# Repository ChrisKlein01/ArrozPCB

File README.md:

# IoT System for Water Management in Rice Paddies

Embedded IoT system for LoRa + GPS telemetry, integrating custom hardware, embedded firmware, iterative PCB design, and a Node-RED backend.

## Final Prototype (V3)

The following images show selected views of the final hardware prototype (V3).

### Enclosure

### Custom PCB

### Auxiliary Modules
For example, Power management and USB to UART modules.

<h2>Firmware Flow Diagram</h2>

## System Overview

End-to-end IoT prototype for wireless telemetry using LoRa communication and GPS data acquisition, covering proof-of-concept validation, custom hardware development, embedded firmware, iterative PCB design, and a complete Node-RED data processing pipeline.

---

## Repository Structure

- `Codigo_lilygo/`  
  Proof-of-concept implementation using a LilyGO T3 v1.6.1 development board. Used for early validation of LoRa communication and end-to-end data flow through an initial Node-RED pipeline before custom PCB and GPS integration.

- `Firmware/`  
  Main embedded firmware for the custom PCB. Handles GPS acquisition, LoRa communication, and system logic.

- `Node Red/`  
  Node-RED flows for telemetry ingestion, processing, and visualization.

- `Envolvente/`  
  Mechanical enclosure design for system housing and protection.

- `V1.0/`  
  First PCB iteration used to validate the custom LoRa hardware.

- `V2.0/`  
  PCB redesign incorporating GPS integration and correcting initial hardware issues.

- `V3.0/`  
  Final PCB revision with optimized layout and complete system integration.

- `.gitignore`  
  Git ignore rules for build artifacts and temporary files.

- `README.md`  
  Project documentation.

---

## Development Flow

1. Proof-of-concept on a LilyGO T3 development board.
2. Validation of LoRa communication and the initial telemetry pipeline using Node-RED.
3. Design and validation of the first custom PCB (V1.0).
4. PCB redesign with GPS integration and hardware improvements (V2.0).
5. Final optimized hardware revision with complete system integration (V3.0).
6. Integration with the Node-RED backend and end-to-end system validation.

---

## Project Scope

The project covers the complete development cycle of an embedded IoT system, including:

- Embedded firmware development (C/C++)
- Custom electronic circuit design
- Schematic capture and PCB design (KiCad)
- PCB assembly and soldering
- LoRa wireless communication
- GPS integration
- MQTT-based telemetry
- Node-RED backend development
- Mechanical enclosure design

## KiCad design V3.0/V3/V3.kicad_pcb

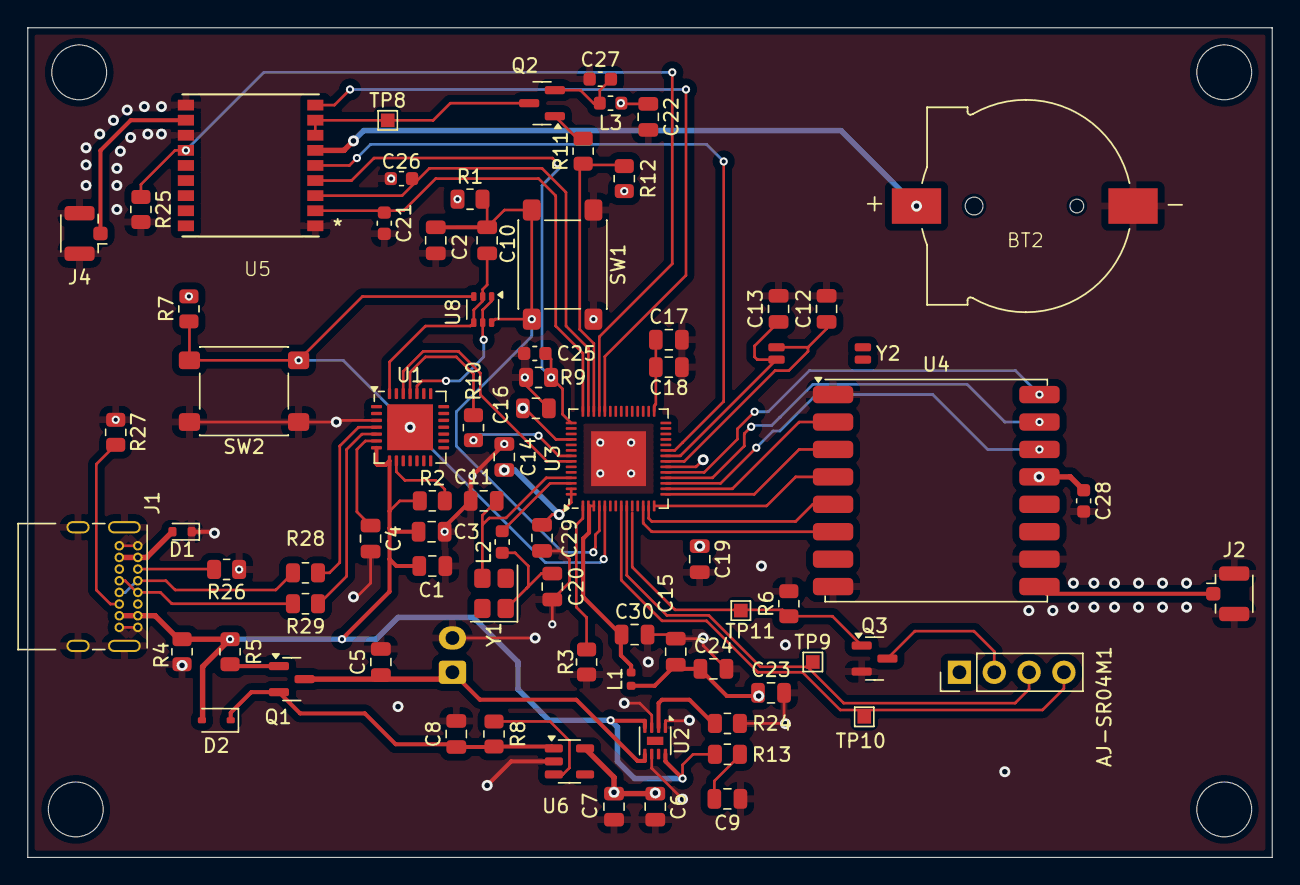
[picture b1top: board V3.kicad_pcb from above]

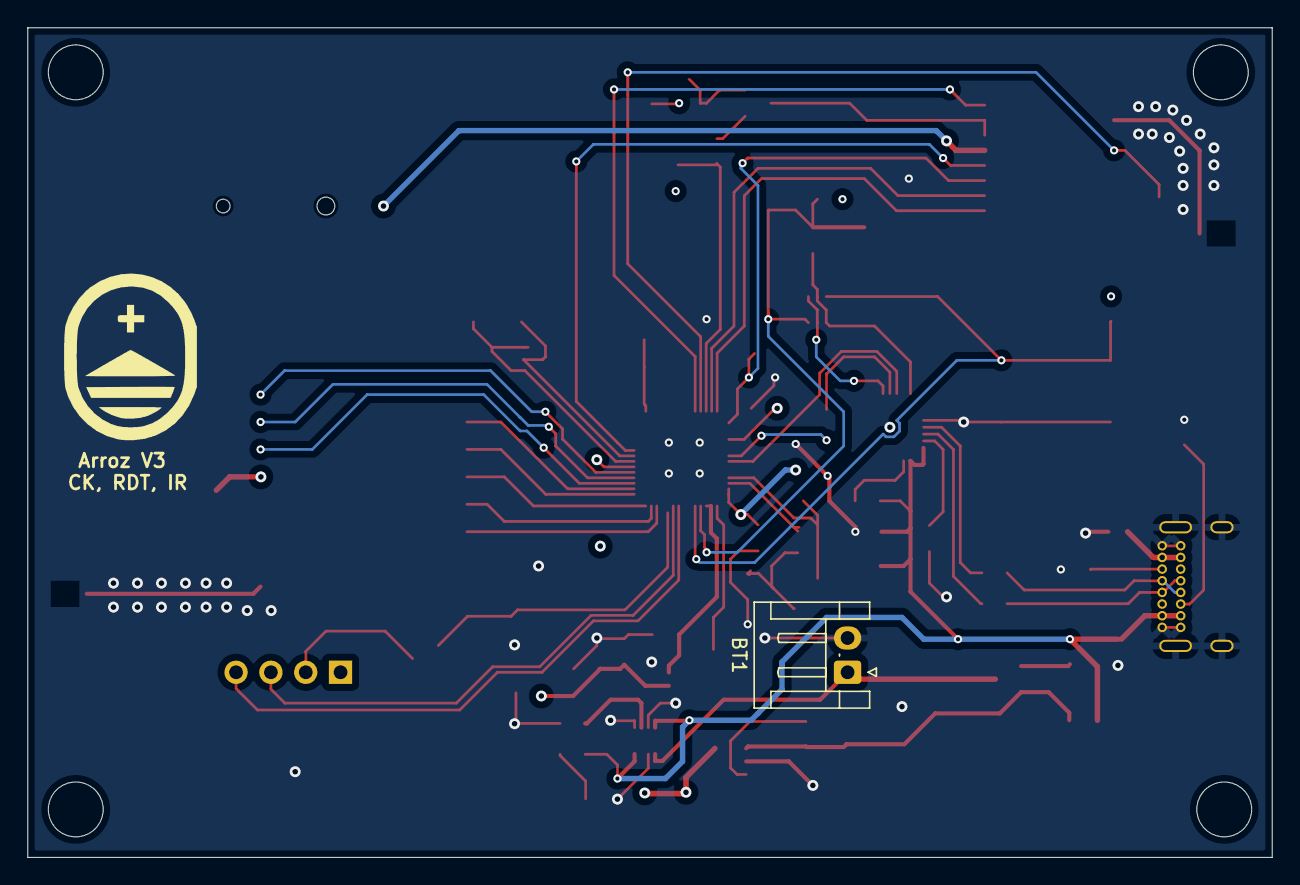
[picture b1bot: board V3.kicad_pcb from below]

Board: 4 copper layers, 90.8 x 60.5 mm, 79 parts (2 on the bottom side), 57 nets.

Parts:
AJ-SR04M1: U3; PinHeader_1x04_P2.54mm_Vertical
BT1: Battery; JST_EH_S2B-EH_1x02_P2.50mm_Horizontal
BT2: 1056TR; pila
C1, C4, C7, C8, C14, C17: 1u; C_0805_2012Metric
C2: 2.2u; C_0805_2012Metric
C3, C10, C16, C18, C19, C30: 0.1u; C_0805_2012Metric
C5, C6, C9, C23: 10u; C_0805_2012Metric
C11: 15p; C_0805_2012Metric
C12, C13: 4.7p; C_0805_2012Metric
C15: 2.2p; C_0805_2012Metric
C20: 18p; C_0805_2012Metric
C21, C25, C26, C27: 56pF; C_0603_1608Metric
C22: 10nF; C_0805_2012Metric
C24: 1.8p; C_0805_2012Metric
C28: 10u; C_0603_1608Metric
C29: 10n; C_0805_2012Metric
D1: RSB6.8S; D_SOD-523
D2: 1N5817WS; D_SOD-323
J1: USB_C_Receptacle_USB2.0_16P; USB_C_Receptacle_GCT_USB4085
J2, J4: Conn_Coaxial_Small; U.FL_Hirose_U.FL-R-SMT-1_Vertical
L1: 2.0n; L_0402_1005Metric
L2: 22n; L_0603_1608Metric
L3: 27nH; L_0603_1608Metric
Q1: AO3401; SOT-23
Q2: AO3401A; SOT-23
Q3: AO3400A; SOT-23
R1, R4, R7, R12, R25: 10k; R_0805_2012Metric
R2: 4.7k; R_0805_2012Metric
R3: 50 NC; R_0805_2012Metric
R5, R11: 1k; R_0805_2012Metric
R6, R8, R9: 100k; R_0805_2012Metric
R10: 499; R_0805_2012Metric
R13: 1R; R_0805_2012Metric
R24: 2k; R_0805_2012Metric
R26, R27: 5.1k; R_0805_2012Metric
R28, R29: 22; R_0805_2012Metric
SW1, SW2: SW_Push; SW_SPST_PTS645Sx43SMTR92
TP8, TP9, TP10, TP11: TestPoint; TestPoint_Pad_1.0x1.0mm
U1: CP2102; QFN-28-1EP_5x5mm_P0.5mm_EP3.35x3.35mm
U2: LGS4056HDA1; DFN-8-1EP_2x2mm_P0.5mm_EP0.6x1.2mm
U3: ESP32-S3FN8; QFN-56-1EP_7x7mm_P0.4mm_EP4x4mm
U4: RFM95W-915S2; HOPERF_RFM9XW_SMD
U5: TESEO-LIV3R; Teseo
U6: AP2112K-3.3TRG1; SOT-23-5
U8: 2n7002bks; SOT-363_SC-70-6
UCU: LOGO; LogoUCU
Y1: Crystal 40MHz/10ppm; Crystal_SMD_3225-4Pin_3.2x2.5mm
Y2: 32.768KHz/ESR≤70KΩ; Crystal_SMD_SeikoEpson_MC146-4Pin_6.7x1.5mm

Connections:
32K_XN: C13.1, U3.22 (XTAL_32K_N), Y2.1
32K_XP: C12.1, U3.21 (XTAL_32K_P), Y2.4
AntOff_GPS: R25.1, U3.39 (GPIO34), U5.13 (ANT_OFF)
CADdetect_LoRa: U3.19 (GPIO14), U4.16 (DIO2)
CHIP_PU: C2.1, C10.1, R1.2, SW1.2, U3.4 (CHIP_PU), U8.6 (D1)
DTR: C10.2, U1.28 (~DTR), U8.2 (G1), U8.4 (S2)
D_N: R29.1, U1.5 (D-)
D_P: R28.1, U1.4 (D+)
ECHO_Sensor: AJ-SR04M1.4 (ECHO), TP10.1, U3.8 (GPIO3)
GND: BT1.2 (-), BT2.N, C1.2, C2.2, C3.2, C4.2, C5.2, C6.2, C7.2, C8.2, C9.2, C11.2, C12.2, C13.2, C14.2, C15.2, C16.2, C17.2, C18.2, C19.2, C20.2, C21.2, C22.2, C23.2, C24.2, C25.2, C26.2, C27.1, C28.2, C29.2, C30.2, D1.1 (K), J1.A1 (GND), J1.A12 (GND), J1.B1 (GND), J1.B12 (GND), J1.S1 (SHIELD), J2.2 (Ext), J4.2 (Ext), Q3.2 (S), R3.2, R4.2, R6.2, R9.2, R24.1, R25.2, R26.1, R27.1, SW1.1, SW2.1, U1.3 (GND), U1.29 (GND), U2.1 (Temp), U2.3 (Gnd), U2.6 (DONE), U3.57 (GND), U4.1 (GND), U4.8 (GND), U4.10 (GND), U5.1 (GND), U5.10 (GND_RF), U5.12 (GND_RF), U6.2 (GND)
MISO_LoRa: U3.15 (GPIO10), U4.3 (MOSI)
MOSI_LoRa: U3.16 (GPIO11), U4.2 (MISO)
NSS_LoRa: U3.13 (GPIO8), U4.5 (NSS)
unnamed: AJ-SR04M1.2 (GND), Q3.3 (D)
unnamed: C9.1, R13.1
unnamed: C30.1, L1.2, U3.2 (VDD3P3), U3.3 (VDD3P3)
unnamed: C8.1, D2.1 (K), Q1.2 (S), R8.1, U6.1 (IN)
unnamed: J1.A5 (CC1), R26.2
unnamed: J1.B5 (CC2), R27.2
unnamed: J1.A6 (D+), J1.B6 (D+), R28.2
unnamed: J1.A7 (D-), J1.B7 (D-), R29.2
unnamed: J2.1 (In), U4.9 (ANT)
unnamed: J4.1 (In), U5.11 (RF_IN)
unnamed: Q1.1 (G), R5.2
unnamed: Q2.3 (D), TP8.1, U5.7 (VCC_IO), U5.8 (VCC)
unnamed: C27.2, L3.2, Q2.2 (S)
unnamed: C4.1, U1.6 (VDD)
unnamed: R2.2, U1.9 (~RST)
unnamed: R24.2, U2.2 (Prog)
unnamed: R11.1, R12.1, U3.40 (GPIO35)
unnamed: R3.1, U3.1 (LNA_IN)
unnamed: R10.2, U3.49 (U0TXD)
unnamed: C17.1, C18.1, U3.29 (VDD_SPI)
unnamed: L2.2, U3.54 (XTAL_P)
unnamed: R8.2, U6.3 (EN)
PPS_GPS: C25.1, R9.1, U3.43 (GPIO38), U5.4 (1PPS)
PWR_Sensor: Q3.1 (G), R6.1, TP11.1, U3.10 (GPIO5)
Pnp_Gps: Q2.1 (G), R11.2
RTS: U1.24 (~RTS), U8.1 (S1), U8.5 (G2)
RXtimeout_LoRa: U3.18 (GPIO13), U4.15 (DIO1)
RX/TXdone_LoRa: U3.17 (GPIO12), U4.14 (DIO0)
Reset_GPS: U3.38 (GPIO33), U5.9 (SYS_RSTn)
Reset_LoRa: U3.12 (GPIO7), U4.6 (RESET)
Rx_GPS: C26.1, U3.41 (GPIO36), U5.3 (RX)
SCK_LoRa: U3.14 (GPIO9), U4.4 (SCK)
TRIG_Sensor: AJ-SR04M1.3 (TRIG), TP9.1, U3.9 (GPIO4)
Tx_GPS: C21.1, U3.42 (GPIO37), U5.2 (TX)
U0RXD: U1.26 (TXD), U3.50 (U0RXD)
U0TXD: R10.1, U1.25 (RXD)
USER_KEY: R7.1, SW2.2, U3.5 (GPIO0), U8.3 (D2)
VBAT: BT1.1 (+), C5.1, Q1.3 (D), U2.5 (BAT)
VBatt: BT2.P, U5.6 (VBATT)
VDD_3V3: AJ-SR04M1.1 (5V), C6.1, C7.1, C14.1, C15.1, C16.1, C19.1, C22.1, C23.1, C24.1, C28.1, C29.1, L1.1, L3.1, R1.1, R7.2, R12.2, U3.20 (VDD3P3_RTC), U3.46 (VDD3P3_CPU), U3.55 (VDDA), U3.56 (VDDA), U4.13 (3.3V), U6.5 (OUT)
VDD_5V: C1.1, C3.1, D1.2 (A), D2.2 (A), J1.A4 (VBUS), J1.A9 (VBUS), J1.B4 (VBUS), J1.B9 (VBUS), R2.1, R4.1, R5.1, R13.2, U1.7 (VREGIN), U1.8 (VBUS), U2.4 (Vcc), U2.8 (CE)
Wake_GPS: U3.23 (GPIO17), U5.5 (Wake-Up)
XTAL_N: C11.1, U3.53 (XTAL_N), Y1.3
XTAL_P: C20.1, L2.1, Y1.1

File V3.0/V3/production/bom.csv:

Designator,Footprint,Quantity,Value,LCSC Part #
AJ-SR04M1,PinHeader_1x04_P2.54mm_Vertical,1,U3,C7243
BT1,JST_EH_S2B-EH_1x02_P2.50mm_Horizontal,1,Battery,
BT2,pila,1,1056TR,C238068
"C1, C14, C17, C4, C7, C8",0805,6,1u,
"C10, C16, C18, C19, C3, C30",0805,6,0.1u,
C11,0805,1,15p,
"C12, C13",0805,2,4.7p,
C15,0805,1,2.2p,
C2,0805,1,2.2u,
C20,0805,1,18p,
"C21, C25, C26, C27",0603,4,56pF,
C22,0805,1,10nF,
"C23, C5, C6, C9",0805,4,10u,
C24,0805,1,1.8p,
C28,0603,1,10u,
C29,0805,1,10n,
D1,D_SOD-523,1,RSB6.8S,C28646388
D2,D_SOD-323,1,1N5817WS,C727114
J1,USB_C_Receptacle_GCT_USB4085,1,USB_C_Receptacle_USB2.0_16P,C7095263
"J2, J4",U.FL_Hirose_U.FL-R-SMT-1_Vertical,2,Conn_Coaxial_Small,C88373
L1,0402,1,2.0n,C18216
L2,0603,1,22n,C12099
L3,0603,1,27nH,C12100
Q1,SOT-23,1,AO3401,C181091
Q2,SOT-23,1,AO3401A,C15127
Q3,SOT-23,1,AO3400A,C20917
"R1, R12, R25, R4, R7",0805,5,10k,
R10,0805,1,499,
"R11, R5",0805,2,1k,
R13,0805,1,1R,
R2,0805,1,4.7k,
R24,0805,1,2k,
"R26, R27",0805,2,5.1k,
"R28, R29",0805,2,22,
R3,0805,1,50 NC,
"R6, R8, R9",0805,3,100k,
"SW1, SW2",SW_SPST_PTS645Sx43SMTR92,2,SW_Push,C49234152
"TP10, TP11, TP8, TP9",TestPoint_Pad_1.0x1.0mm,4,TestPoint,
U1,QFN-28-1EP_5x5mm_P0.5mm_EP3.35x3.35mm,1,CP2102,C6568
U2,DFN-8-1EP_2x2mm_P0.5mm_EP0.6x1.2mm,1,LGS4056HDA1,C5124109
U3,QFN-56-1EP_7x7mm_P0.4mm_EP4x4mm,1,ESP32-S3FN8,C2913196
U4,HOPERF_RFM9XW_SMD,1,RFM95W-915S2,
U5,Teseo,1,TESEO-LIV3R,
U6,SOT-23-5,1,AP2112K-3.3TRG1,C23380830
U8,SOT-363_SC-70-6,1,2n7002bks,C68181
Y1,Crystal_SMD_3225-4Pin_3.2x2.5mm,1,Crystal 40MHz/10ppm,C5380316
Y2,Crystal_SMD_SeikoEpson_MC146-4Pin_6.7x1.5mm,1,32.768KHz/ESR≤70KΩ,C15482

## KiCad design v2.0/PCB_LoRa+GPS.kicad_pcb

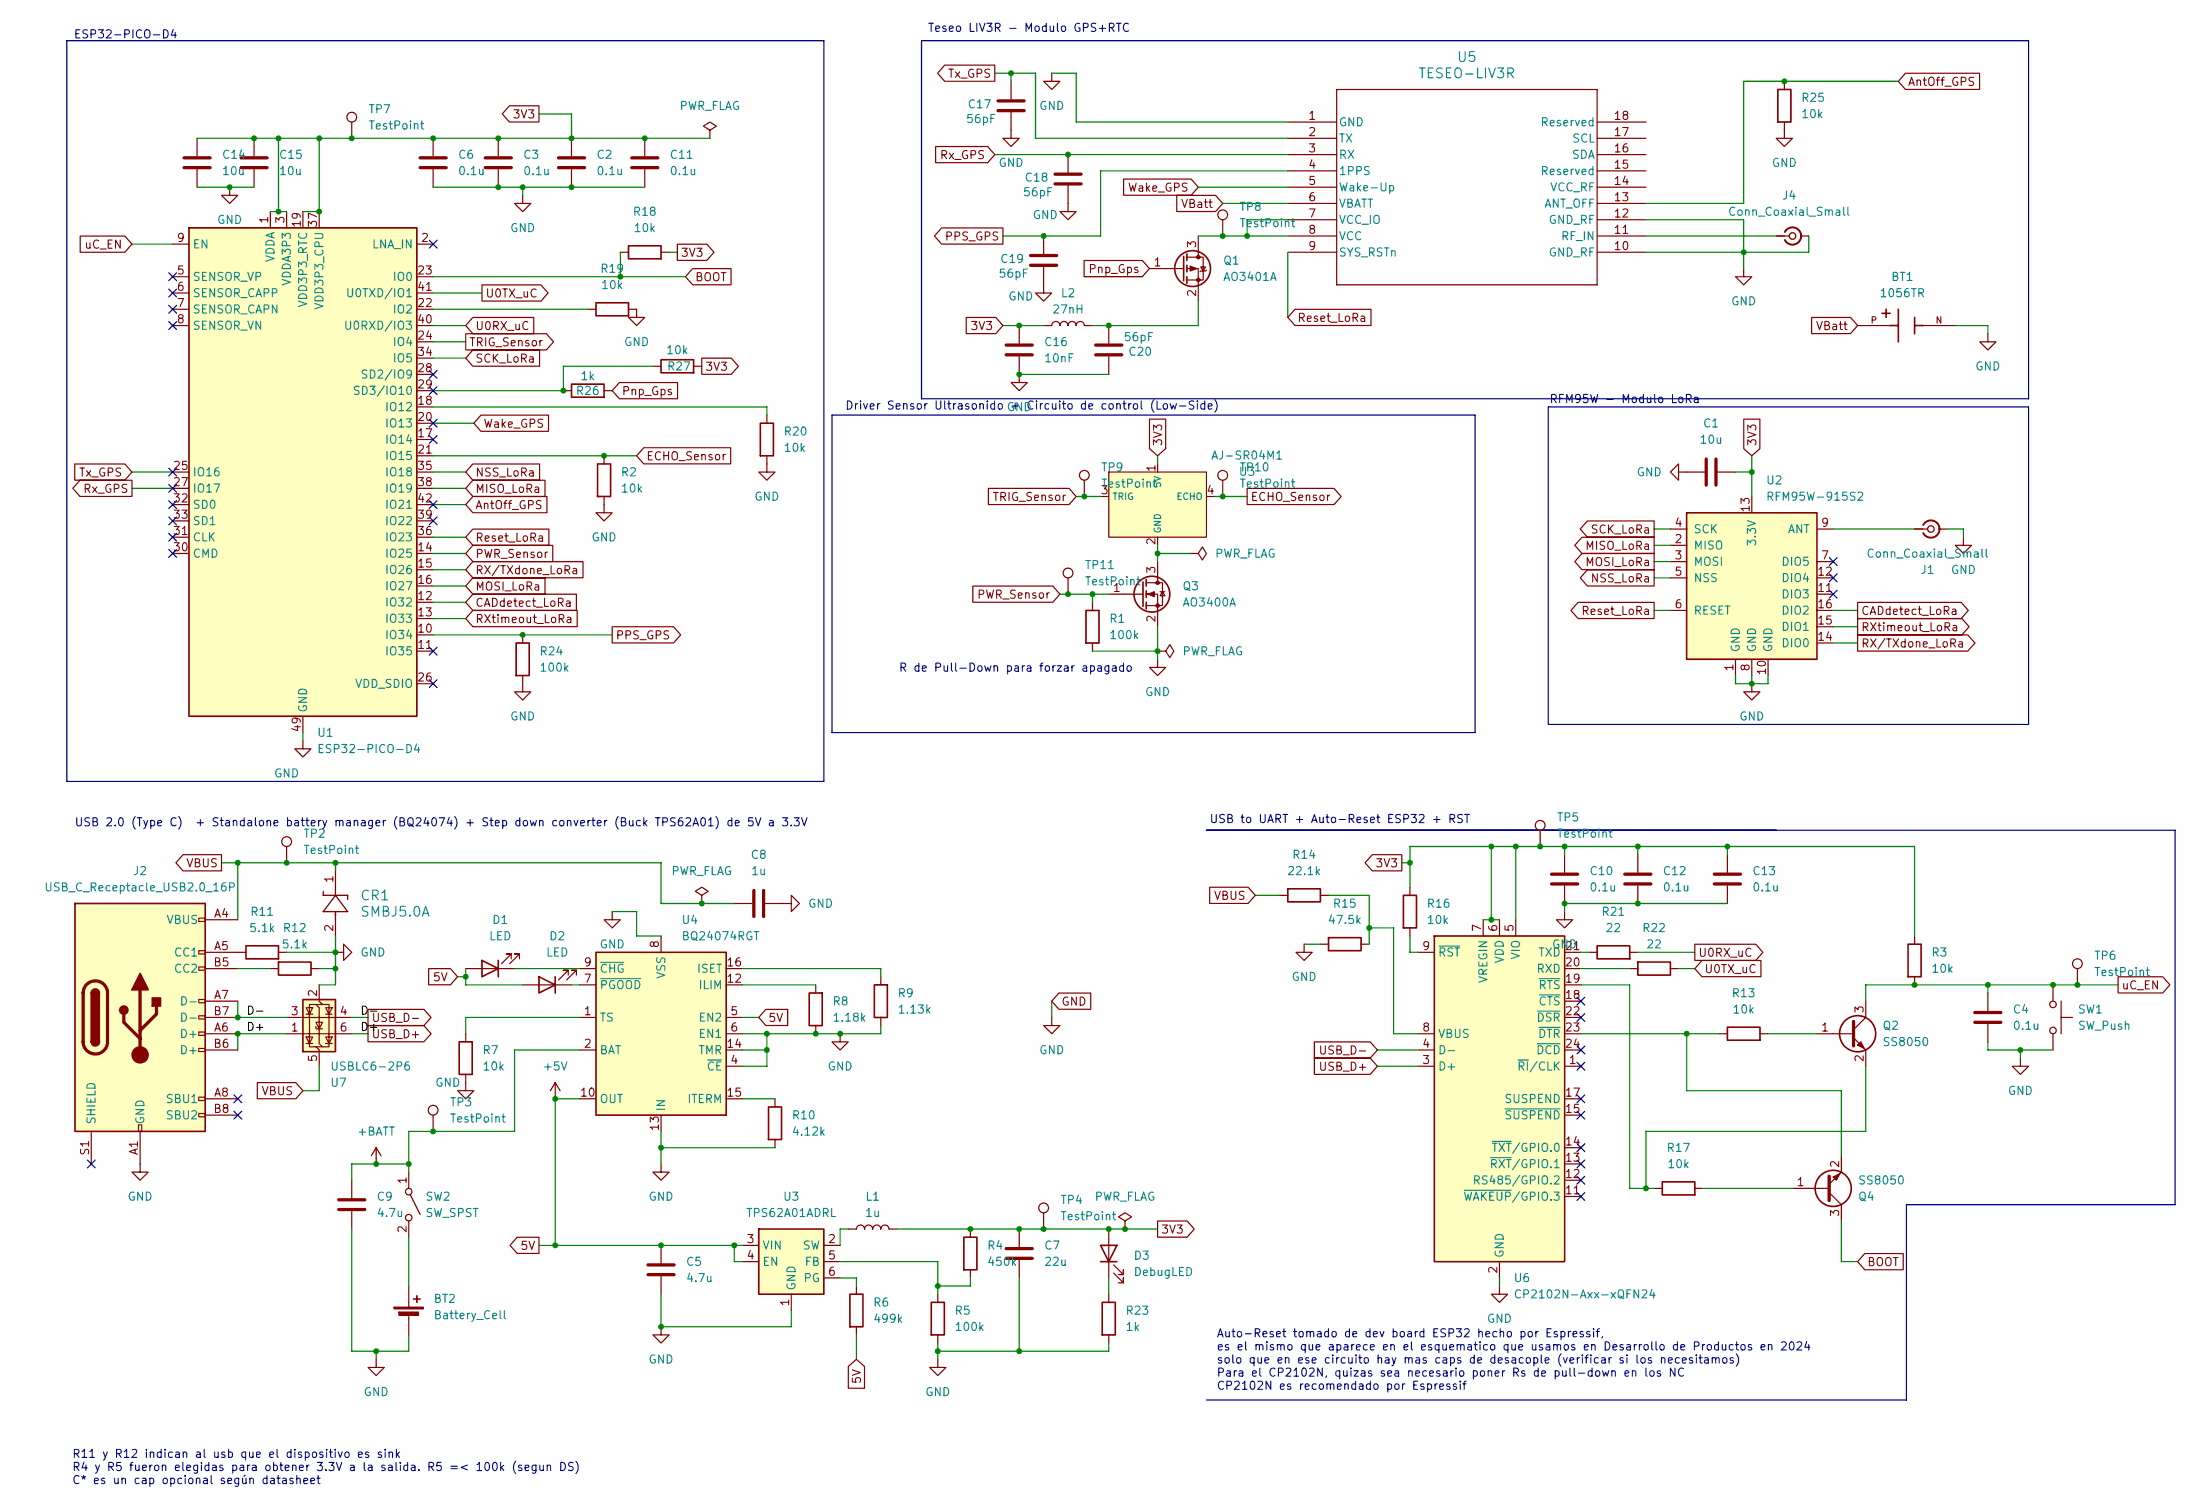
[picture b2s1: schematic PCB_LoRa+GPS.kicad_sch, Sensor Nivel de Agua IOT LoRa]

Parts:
AJ-SR04M1: U3; PinSocket_1x04_P1.00mm_Vertical
BT1: 1056TR; BAT_1056TR; PARTREV D
BT2: Battery_Cell; JST_EH_S2B-EH_1x02_P2.50mm_Horizontal
C1, C14, C15: 10u; C_0603_1608Metric
C2, C3, C4, C6, C10, C11, C12, C13: 0.1u; C_0402_1005Metric
C5: 4.7u; C_0603_1608Metric
C7: 22u; C_0805_2012Metric
C8: 1u; C_0402_1005Metric
C9: 4.7u; C_0402_1005Metric
C16: 10nF; C_0805_2012Metric
C17, C18, C19, C20: 56pF; C_0603_1608Metric
CR1: SMBJ5.0A; D_SMB
D1, D2: LED; LED_0603_1608Metric
D3: DebugLED; LED_0603_1608Metric
J1, J4: Conn_Coaxial_Small; U.FL_Hirose_U.FL-R-SMT-1_Vertical
J2: USB_C_Receptacle_USB2.0_16P; USB_C_Receptacle_GCT_USB4085
L1: 1u; L_0805_2012Metric
L2: 27nH; L_0805_2012Metric
Q1: AO3401A; SOT-23
Q2, Q4: SS8050; SOT-23
Q3: AO3400A; SOT-23
R1, R5, R24: 100k; R_0402_1005Metric
R2, R3, R7, R13, R16, R17, R18, R19, R20, R25, R27: 10k; R_0402_1005Metric
R4: 450k; R_0402_1005Metric
R6: 499k; R_0402_1005Metric
R8: 1.18k; R_0402_1005Metric
R9: 1.13k; R_0402_1005Metric
R10: 4.12k; R_0402_1005Metric
R11, R12: 5.1k; R_0402_1005Metric
R14: 22.1k; R_0402_1005Metric
R15: 47.5k; R_0402_1005Metric
R21, R22: 22; R_0402_1005Metric
R23, R26: 1k; R_0402_1005Metric
SW1: SW_Push; SW_Push_1P1T_NO_CK_KMR2
SW2: SW_SPST; SW_E-Switch_EG1271_SPDT
TP2, TP3, TP4, TP5, TP6, TP7, TP8, TP9, TP10, TP11: TestPoint; TestPoint_Pad_1.0x1.0mm
U1: ESP32-PICO-D4; QFN-48-1EP_7x7mm_P0.5mm_EP5.3x5.3mm
U2: RFM95W-915S2; HOPERF_RFM9XW_SMD
U3: TPS62A01ADRL; SOT-563
U4: BQ24074RGT; VQFN-16-1EP_3x3mm_P0.5mm_EP1.6x1.6mm
U5: TESEO-LIV3R; ARRAY_LIV3R_STM
U6: CP2102N-Axx-xQFN24; QFN-24-1EP_4x4mm_P0.5mm_EP2.6x2.6mm
U7: USBLC6-2P6; SOT-666

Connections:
3V3: AJ-SR04M1.1 (5V), C1.1, C2.1, C3.1, C6.1, C7.1, C10.1, C11.1, C12.1, C13.1, C14.1, C15.1, C16.1, D3.2 (A), L1.2, L2.1, R3.1, R4.1, R16.1, R18.2, R27.2, TP4.1, TP5.1, TP7.1, U1.1 (VDDA), U1.3 (VDDA3P3), U1.4 (VDDA3P3), U1.19 (VDD3P3_RTC), U1.37 (VDD3P3_CPU), U1.43 (VDDA), U1.46 (VDDA), U2.13 (3.3V), U6.5 (VIO), U6.6 (VDD), U6.7 (VREGIN)
5V: C5.1, D1.2 (A), D2.2 (A), R6.2, U3.3 (VIN), U3.4 (EN), U4.5 (EN2), U4.10 (OUT), U4.11 (OUT)
+BATT: C9.1, SW2.1 (A), TP3.1, U4.2 (BAT), U4.3 (BAT)
AntOff_GPS: R25.1, U1.42 (IO21), U5.13 (ANT_OFF)
BOOT: Q4.3 (C), R18.1, U1.23 (IO0)
CADdetect_LoRa: U1.12 (IO32), U2.16 (DIO2)
ECHO_Sensor: AJ-SR04M1.4 (ECHO), R2.1, TP10.1, U1.21 (IO15)
GND: BT1.N, BT2.2 (-), C1.2, C2.2, C3.2, C4.2, C5.2, C6.2, C7.2, C8.1, C9.2, C10.2, C11.2, C12.2, C13.2, C14.2, C15.2, C16.2, C17.2, C18.2, C19.2, C20.1, CR1.2, J1.2 (Ext), J2.A1 (GND), J2.A12 (GND), J2.B1 (GND), J2.B12 (GND), J4.2 (Ext), Q3.2 (S), R1.2, R2.2, R5.2, R7.1, R8.1, R9.1, R10.2, R11.2, R12.1, R15.2, R19.2, R20.2, R23.2, R24.2, R25.2, SW1.2, U1.49 (GND), U2.1 (GND), U2.8 (GND), U2.10 (GND), U3.1 (GND), U4.4 (~CE), U4.6 (EN1), U4.8 (VSS), U4.13 (IN), U4.14 (TMR), U4.17 (VSS), U5.1 (GND), U5.10 (GND_RF), U5.12 (GND_RF), U6.2 (GND), U6.25 (GND), U7.2 (GND); also elsewhere on the board
MISO_LoRa: U1.38 (IO19), U2.2 (MISO)
MOSI_LoRa: U1.16 (IO27), U2.3 (MOSI)
NSS_LoRa: U1.35 (IO18), U2.5 (NSS)
unnamed: AJ-SR04M1.2 (GND), Q3.3 (D)
unnamed: BT2.1 (+), SW2.2 (B)
unnamed: D1.1 (K), U4.9 (~CHG)
unnamed: D2.1 (K), U4.7 (~PGOOD)
unnamed: D3.1 (K), R23.1
unnamed: J1.1 (In), U2.9 (ANT)
unnamed: J2.A5 (CC1), R11.1
unnamed: J2.B5 (CC2), R12.2
unnamed: J4.1 (In), U5.11 (RF_IN)
unnamed: Q1.3 (D), TP8.1, U5.7 (VCC_IO), U5.8 (VCC)
unnamed: C20.2, L2.2, Q1.2 (S)
unnamed: Q2.1 (B), R13.2
unnamed: Q2.2 (E), R17.1, U6.19 (~RTS)
unnamed: Q4.1 (B), R17.2
unnamed: Q4.2 (E), R13.1, U6.23 (~DTR)
unnamed: R19.1, U1.22 (IO2)
unnamed: R20.1, U1.18 (IO12)
unnamed: R4.2, R5.1, U3.5 (FB)
unnamed: R6.1, U3.6 (PG)
unnamed: L1.1, U3.2 (SW)
unnamed: R8.2, U4.12 (ILIM)
unnamed: R9.2, U4.16 (ISET)
unnamed: R10.1, U4.15 (ITERM)
unnamed: R7.2, U4.1 (TS)
unnamed: R22.2, U6.20 (RXD)
unnamed: R21.1, U6.21 (TXD)
unnamed: R14.1, R15.1, U6.8 (VBUS)
unnamed: R16.2, U6.9 (~RST)
PPS_GPS: C19.1, R24.1, U1.10 (IO34), U5.4 (1PPS)
PWR_Sensor: Q3.1 (G), R1.1, TP11.1, U1.14 (IO25)
Pnp_Gps: Q1.1 (G), R26.2
RXtimeout_LoRa: U1.13 (IO33), U2.15 (DIO1)
RX/TXdone_LoRa: U1.15 (IO26), U2.14 (DIO0)
Reset_LoRa: U1.36 (IO23), U2.6 (RESET), U5.9 (SYS_RSTn)
Rx_GPS: C18.1, U1.27 (IO17), U5.3 (RX)
SCK_LoRa: U1.34 (IO5), U2.4 (SCK)
TRIG_Sensor: AJ-SR04M1.3 (TRIG), TP9.1, U1.24 (IO4)
Tx_GPS: C17.1, U1.25 (IO16), U5.2 (TX)
U0RX_uC: R21.2, U1.40 (U0RXD/IO3)
U0TX_uC: R22.1, U1.41 (U0TXD/IO1)
USB_D+: J2.A6 (D+), J2.B6 (D+), U6.3 (D+), U7.1 (I/O1), U7.6 (I/O1)
USB_D-: J2.A7 (D-), J2.B7 (D-), U6.4 (D-), U7.3 (I/O2), U7.4 (I/O2)
VBUS: C8.2, CR1.1, J2.A4 (VBUS), J2.A9 (VBUS), J2.B4 (VBUS), J2.B9 (VBUS), R14.2, TP2.1, U7.5 (VBUS)
VBatt: BT1.P, U5.6 (VBATT)
Wake_GPS: U1.20 (IO13), U5.5 (Wake-Up)
uC_EN: C4.1, Q2.3 (C), R3.2, SW1.1, TP6.1, U1.9 (EN)

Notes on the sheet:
Auto-Reset tomado de dev board ESP32 hecho por Espressif, es el mismo que aparece en el esquematico que usamos en Desarrollo de Productos en 2024 solo que en ese circuito hay mas caps de desacople (verificar si los necesitamos) Para el CP2102N, quizas sea necesario poner Rs de pull-down en los NC C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
USB to UART + Auto-Reset ESP32 + RST
Driver Sensor Ultrasonido + Circuito de control (Low-Side)
USB 2.0 (Type C) + Standalone battery manager (BQ24074) + Step down converter (Buck TPS62A01) de 5V a 3.3V
ESP32-PICO-D4
R de Pull-Down para forzar apagado
R11 y R12 indican al usb que el dispositivo es sink R4 y R5 fueron elegidas para obtener 3.3V a la salida. R5 =< 100k (segun DS) C* es un cap opcional según datasheet
RFM95W - Modulo LoRa
Teseo LIV3R - Modulo GPS+RTC

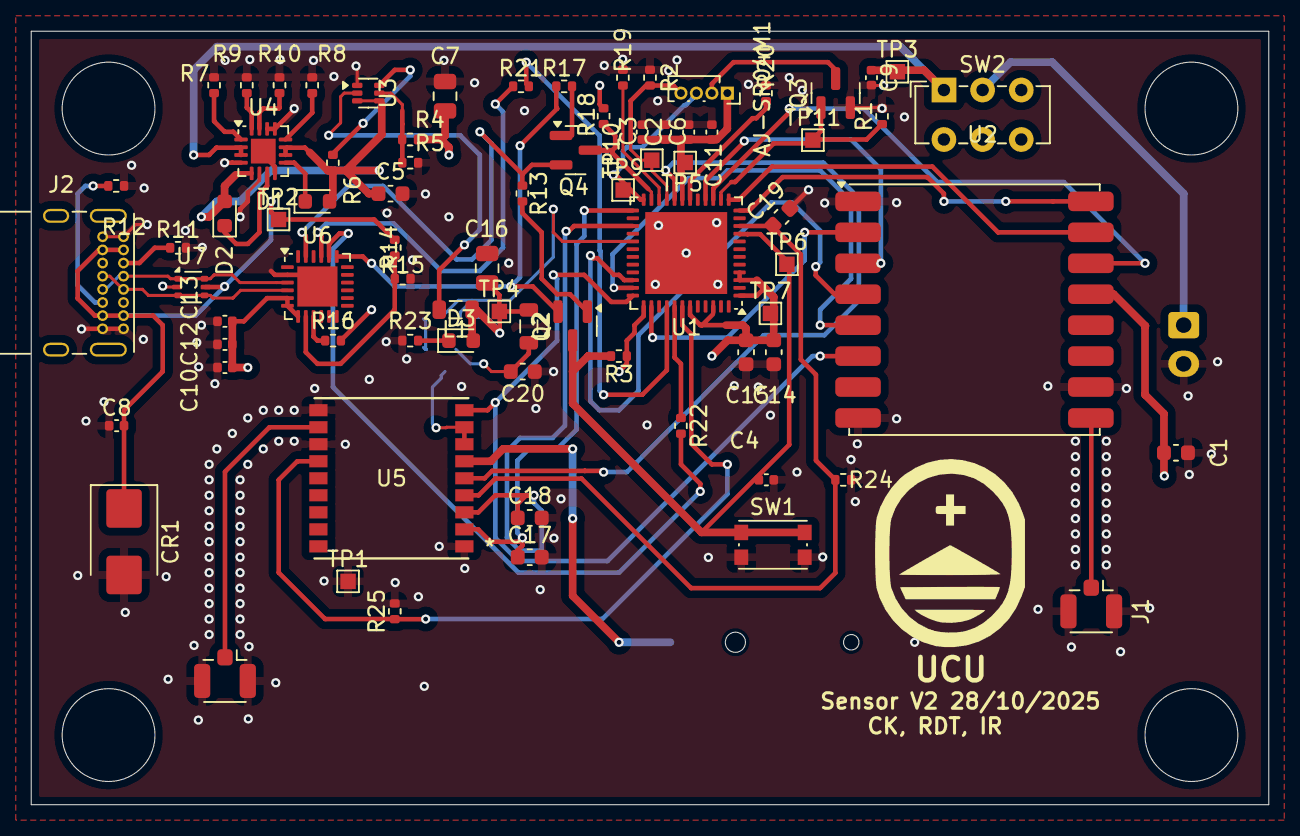
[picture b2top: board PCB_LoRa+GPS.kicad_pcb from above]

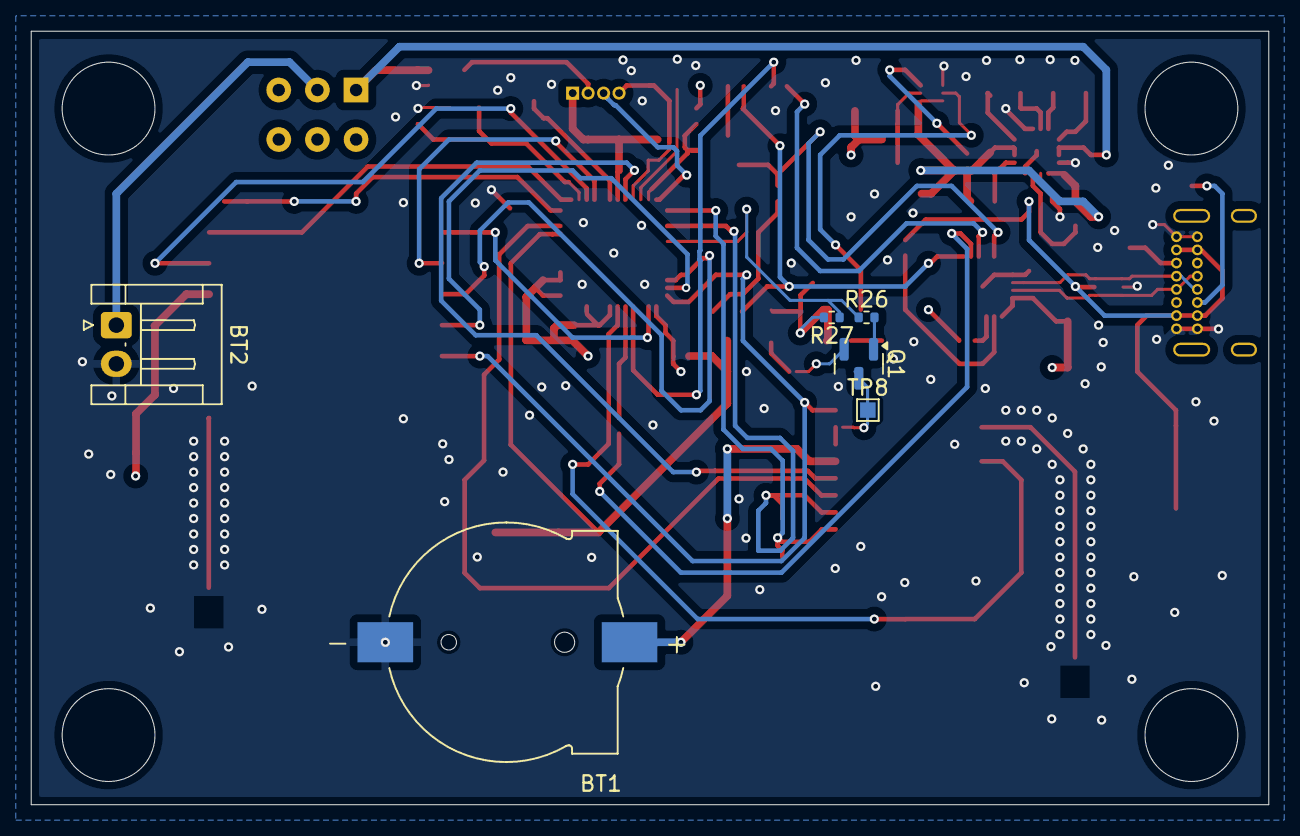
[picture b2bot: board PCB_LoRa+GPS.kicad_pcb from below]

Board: 4 copper layers, 80.0 x 50.0 mm, 84 parts (6 on the bottom side), 57 nets.

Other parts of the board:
TP1: TestPoint; TestPoint_Pad_1.0x1.0mm
UCU: LOGO; LogoUCU

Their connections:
GND: TP1.1; also elsewhere on the board

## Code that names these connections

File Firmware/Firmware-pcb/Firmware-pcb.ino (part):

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
#define GPS_RX      37
#define GPS_TX      36
#define PNP_GPS     35
#define RESET_GPS   33
#define PPS_PIN     38
#define ANT_OFF     34   // Output del Teseo — solo INPUT, no usar como salida
#define WAKE_GPS    17   // No utilizado

// ============================================================================
// CONFIGURACIÓN
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}

void gpsEncender() {
    pinMode(PNP_GPS,   OUTPUT);
    pinMode(RESET_GPS, OUTPUT);

    digitalWrite(PNP_GPS, HIGH);
    delay(50);
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        Serial.println("[GPS] GPS solicitado — corriendo antes del TX...");
        gpsRunYApagar();
    } else {
        pinMode(PNP_GPS,   OUTPUT);
        pinMode(RESET_GPS, OUTPUT);
        digitalWrite(PNP_GPS,   HIGH);
        digitalWrite(RESET_GPS, HIGH);
        if (!firstBoot) {
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
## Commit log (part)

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2025-08-19 Inicial: proyecto KiCad
2025-08-20 Mejoras de lo ya ruteado / falta uc
2025-08-21 falta uc
2025-09-22 Revision general pcb
2025-10-05 mounting holes
2025-10-06 Create lilygo_lora_ok
2025-10-06 lilygo_lora_ok.ino
2025-10-18 V1 a revisar
2025-10-19 LoRa+G¨S
2025-10-21 agregadas capas de power y gnd
2025-10-25 Pcb v1
2025-10-28 V1 final
2025-10-28 Pcb v1.0
2025-10-28 V1 + via rules .3mm
2025-10-28 V2 +Q1 (Falta DRS)
2025-10-28 V2 DRC - Revisar
2025-10-28 agregados pads
2025-10-28 Pads, v1 de chris (sin LoRa+GPS)
2025-10-28 pads, gerbers, logo ucu, iniciales y fecha
2025-10-29 V2 DRC checked
2025-10-29 Varicela y footpads
2025-10-29 correcciones drc
2025-10-29 V2 Gerbers
2025-10-30 V2 Gerbers corregidos
2025-12-17 v3schem
2025-12-17 ¨v3¨
2025-12-18 falta rutear esp v3
2025-12-18 Version 3 completa tal como en PC
2025-12-18 v3 para revisar
2025-12-20 V3 para revisarr
2025-12-20 V3 para revisarrrrr
2025-12-21 V3 final
2026-03-07 Firmware Final
2026-03-21 Nodered
2026-03-22 Final
2026-03-23 Create Archivo .ipt del envolvente
